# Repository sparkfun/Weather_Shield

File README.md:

SparkFun Weather Shield
========================

[*SparkFun Weather Shield (DEV-13956)*](https://www.sparkfun.com/products/13956)

Weather Shield is an Arduino shield that gathers relative humidity, barometric pressure, temperature, light intensity, as well as optional rain, wind direction, and wind speed (using optional [external weather gauges](https://www.sparkfun.com/products/8942)).

Repository Contents
------------------

* **/Firmware** - Example Arduino sketch to demostrate how to read from the various sensors.
* **/Fritzing** - Fritzing Example wiring images
* **/Hardware** - All the Eagle PCB design files (.brd, .sch).
* **/Production** - Test bed files and production panel files

Documentation
--------------
* **[Installing an Arduino Library Guide](https://learn.sparkfun.com/tutorials/installing-an-arduino-library)** - Basic information on how to install an Arduino library.
* **[MPL3115A2 Library](https://github.com/sparkfun/SparkFun_MPL3115A2_Breakout_Arduino_Library)** - MPL3115A2 library required for Weather Shield examples. 
* **[Si7021 Library](https://github.com/sparkfun/SparkFun_Si701_Breakout_Arduino_Library)** - Si7021 humidity sensor library required for Weather Shield examples. 
* **[Hookup Guide](https://learn.sparkfun.com/tutorials/arduino-weather-shield-hookup-guide-v12)** - Basic hookup guide for the Weather Shield v1.2.
* **[SparkFun Fritzing repo](https://github.com/sparkfun/Fritzing_Parts)** - Fritzing diagrams for SparkFun products.
* **[SparkFun 3D Model repo](https://github.com/sparkfun/3D_Models)** - 3D models of SparkFun products. 
* _**[HTU21D Library](https://github.com/sparkfun/SparkFun_HTU21D_Breakout_Arduino_Library)** - The HTU21D humidity sensor was used on DEV-12081 and prior versions of the Weather Shield so if you have an older version you may need this library to run the examples._

Product Versions
----------------
* [DEV-13956](https://www.sparkfun.com/products/13956)- V1.2 w/ Si7021
* _[DEV-12081 (Retired)](https://www.sparkfun.com/products/13956)- HTU21D_

Version History
---------------
* [v1.2](https://github.com/sparkfun/Weather_Shield/releases/tag/v1.2) - Latest Version
* [v1.1](https://github.com/sparkfun/Weather_Shield/releases/tag/v1.1) - Initial Release

License Information
-------------------

This product is _**open source**_! 

Please review the LICENSE.md file for license information. 

If you have any questions or concerns on licensing, please contact techsupport@sparkfun.com.

Distributed as-is; no warranty is given.

- Your friends at SparkFun.

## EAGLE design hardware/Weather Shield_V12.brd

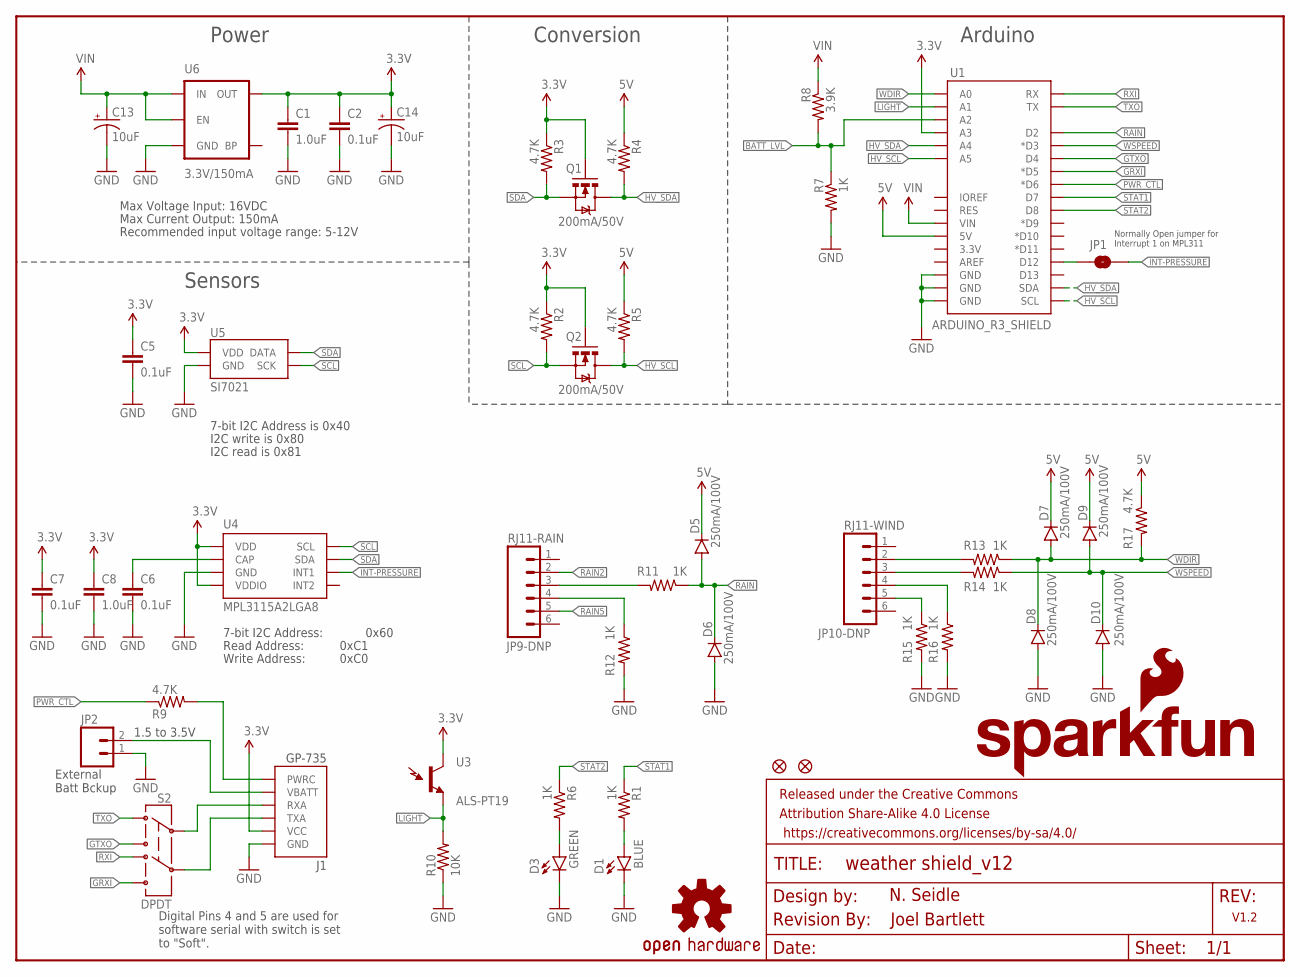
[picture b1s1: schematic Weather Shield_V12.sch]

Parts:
C1, C8: 1.0uF; 0603-CAP
C2, C5, C6, C7: 0.1uF; 0603-CAP
C13, C14: 10uF; EIA3216
D1: BLUE; LED-0603
D3: GREEN; LED-0603
D5, D6, D7, D8, D9, D10: 250mA/100V; SOD-323
FD1, FD2: FIDUCIAL1X2; FIDUCIAL-1X2
FRAME1: FRAME-LETTER; CREATIVE_COMMONS
J1: GP-735; GP-635T
JP1: JUMPER-PAD-2-NO; PAD-JUMPER-2-NO_NO_SILK
JP2: External Batt Bckup; 1X02
JP9-DNP: RJ11-RAIN; RJ11-6
JP10-DNP: RJ11-WIND; RJ11-6
LOGO1: OSHW-LOGOM; OSHW-LOGO-M
LOGO2: SFE_LOGO_NAME_FLAME.1_INCH; SFE_LOGO_NAME_FLAME_.1
Q1, Q2: 200mA/50V; SOT23-3
R1, R6, R7, R11, R12, R13, R14, R15, R16: 1K; 0603-RES
R2, R3, R4, R5, R9, R17: 4.7K; 0603-RES
R8: 3.9K; 0603
R10: 10K; 0603-RES
S2: DPDT; AYZ0202
U1: ARDUINO_R3_SHIELD; UNO_R3_SHIELD
U3: ALS-PT19
U4: MPL3115A2LGA8; LGA8
U5: SI7021
U6: 3.3V/150mA; SOT23-5
U$2: REVISION

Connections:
3.3V: C1.1, C2.1, C5.1, C7.1, C8.1, C14.A (+), J1.2 (VCC), Q1.1 (G), Q2.1 (G), R2.1, R3.1, U1.A3, U3.C (C1), U4.1 (VDD), U4.4 (VDDIO), U5.VDD, U6.5 (OUT)
3V_PWR_CTL: J1.6 (PWRC), R9.2
5V: D5.C, D7.C, D9.C, R4.1, R5.1, R17.1, U1.5V
BATT_LVL: R7.1, R8.2, U1.A2
GND: C1.2, C2.2, C5.2, C6.2, C7.2, C8.2, C13.C (-), C14.C (-), D1.C, D3.C, D6.A, D8.A, D10.A, J1.1 (GND), JP2.1, R7.2, R10.1, R12.2, R15.2, R16.2, U1.GND@0 (GND), U1.GND@1 (GND), U1.GND@2 (GND), U4.3 (GND), U5.GND, U6.2 (GND)
GPS-RX: J1.4 (RXA), S2.2
GPS-TX: J1.3 (TXA), S2.5
GRXI: S2.6, U1.D5 (*D5)
GTXO: S2.3, U1.D4
HV_SCL: Q2.3 (D), R5.2, U1.A5, U1.SCL
HV_SDA: Q1.3 (D), R4.2, U1.A4, U1.SDA
INT-PRESSURE: JP1.2, U4.6 (INT1)
LIGHT: R10.2, U1.A1, U3.E (E1)
unnamed: JP10-DNP.3, R14.2
unnamed: JP10-DNP.2, R13.2
unnamed: D1.A, R1.2
unnamed: JP9-DNP.3, R11.2
unnamed: C6.1, U4.2 (CAP)
unnamed: JP1.1, U1.D12
unnamed: D3.A, R6.2
unnamed: JP9-DNP.4, R12.1
unnamed: JP10-DNP.5, R15.1
unnamed: JP10-DNP.4, R16.1
PWR_CTL: R9.1, U1.D6 (*D6)
RAIN: D5.A, D6.C, R11.1, U1.D2
RAIN2: JP9-DNP.2
RAIN5: JP9-DNP.5
RXI: S2.4, U1.RX
SCL: Q2.2 (S), R2.2, U4.8 (SCL), U5.SCK
SDA: Q1.2 (S), R3.2, U4.7 (SDA), U5.DATA
STAT1: R1.1, U1.D7
STAT2: R6.1, U1.D8
TXO: S2.1, U1.TX
VIN: C13.A (+), R8.1, U1.VIN, U6.1 (IN), U6.3 (EN)
V_BATT: J1.5 (VBATT), JP2.2
WDIR: D7.A, D8.C, R13.1, R17.2, U1.A0
WSPEED: D9.A, D10.C, R14.1, U1.D3 (*D3)

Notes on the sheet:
Max Voltage Input: 16VDC
Max Current Output: 150mA
N. Seidle
Read Address:
Write Address:
7-bit I2C Address:
0x60
0xC1
0xC0
7-bit I2C Address is 0x40
I2C write is 0x80
I2C read is 0x81
1.5 to 3.5V
External Batt Bckup
Sensors
Power
Conversion
Arduino
V1.2
Digital Pins 4 and 5 are used for software serial with switch is set to "Soft".
Joel Bartlett
Recommended input voltage range: 5-12V
Normally Open jumper for Interrupt 1 on MPL311

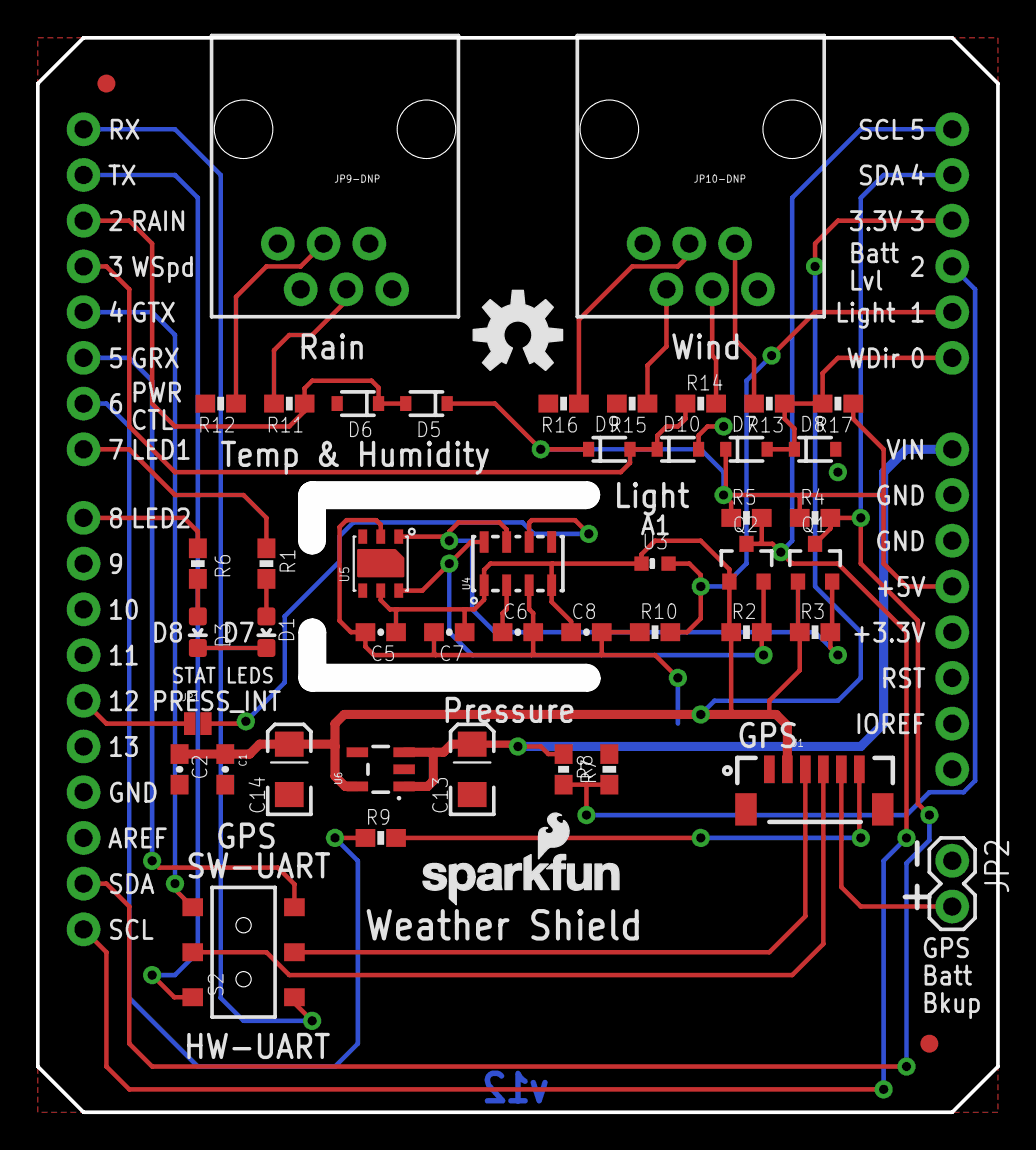
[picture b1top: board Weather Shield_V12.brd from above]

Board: 2 copper layers, 52.0 x 58.4 mm, 52 parts (0 on the bottom side), 35 nets.

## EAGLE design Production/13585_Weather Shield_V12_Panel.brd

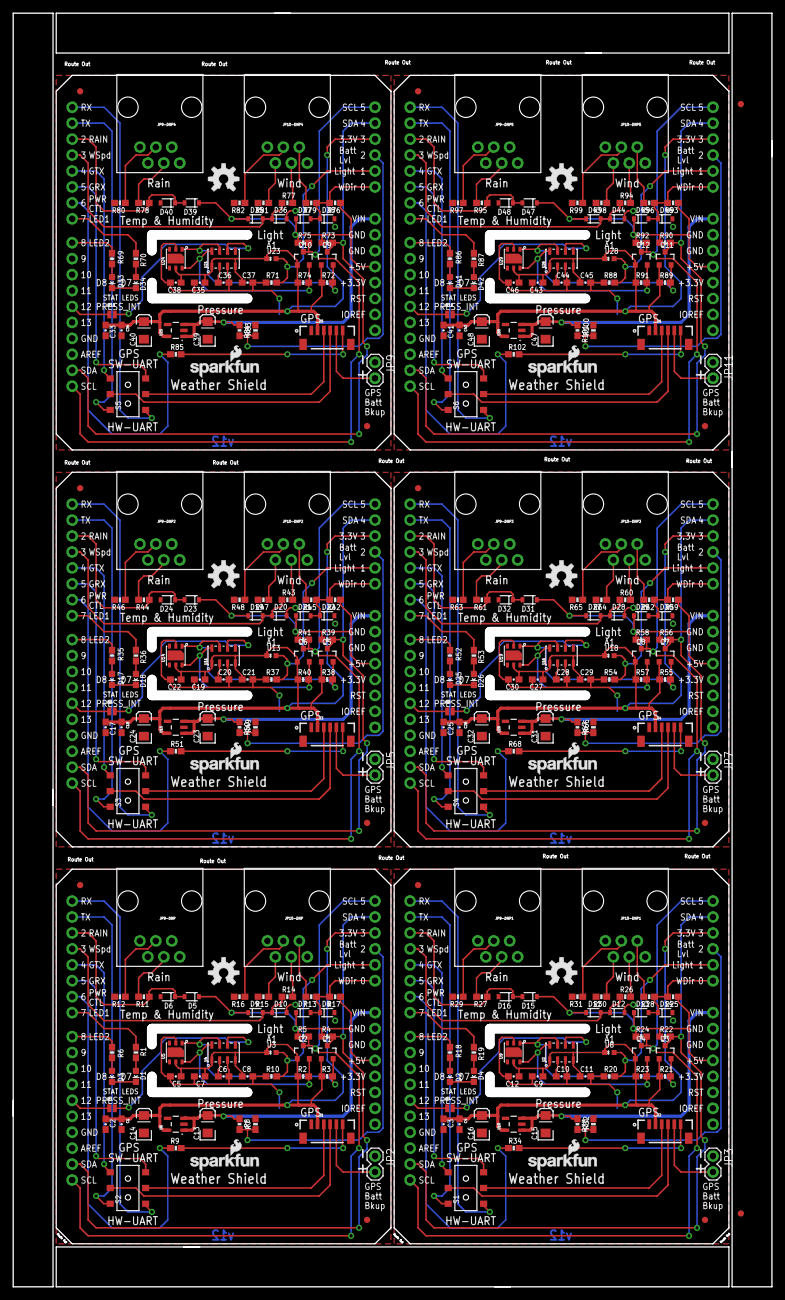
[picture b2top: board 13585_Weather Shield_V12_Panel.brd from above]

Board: 2 copper layers, 119.6 x 201.6 mm, 302 parts (0 on the bottom side), 210 nets.

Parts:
C1, C4, C8, C11, C18, C21, C26, C29, C34, C37, C42, C45: 1.0uF; 0603-CAP
C2, C3, C5, C6, C7, C9, C10, C12, C17, C19, C20, C22, C25, C27, C28, C30, C33, C35, C36, C38, C41, C43, C44, C46: 0.1uF; 0603-CAP
C13, C14, C15, C16, C23, C24, C31, C32, C39, C40, C47, C48: 10uF; EIA3216
D1, D4, D18, D26, D34, D42: BLUE; LED-0603
D2, D3, D17, D25, D33, D41: GREEN; LED-0603
D5, D6, D7, D8, D9, D10, D11, D12, D13, D14, D15, D16, D19, D20, D21, D22, D23, D24, D27, D28, D29, D30, D31, D32, D35, D36, D37, D38, D39, D40, D43, D44, D45, D46, D47, D48: 250mA/100V; SOD-323
E$7, E$8: FIDUCIAL-1X2
FD1, FD2, FD3, FD4, FD5, FD6, FD7, FD8, FD9, FD10, FD11, FD12: FIDUCIAL1X2; FIDUCIAL-1X2
J1, J2, J3, J4, J5, J6: GP-735; GP-635T
JP1, JP4, JP6, JP8, JP10, JP12: PAD-JUMPER-2-NO_NO_SILK
JP2, JP3, JP5, JP7, JP9, JP11: External Batt Bckup; 1X02
JP9-DNP, JP9-DNP1, JP9-DNP2, JP9-DNP3, JP9-DNP4, JP9-DNP5: RJ11-RAIN; RJ11-6
JP10-DNP, JP10-DNP1, JP10-DNP2, JP10-DNP3, JP10-DNP4, JP10-DNP5: RJ11-WIND; RJ11-6
LOGO1, LOGO4, LOGO6, LOGO8, LOGO10, LOGO12: OSHW-LOGOM; OSHW-LOGO-M
LOGO2, LOGO3, LOGO5, LOGO7, LOGO9, LOGO11: SFE_LOGO_NAME_FLAME.1_INCH; SFE_LOGO_NAME_FLAME_.1
Q1, Q2, Q3, Q4, Q5, Q6, Q7, Q8, Q9, Q10, Q11, Q12: 200mA/50V; SOT23-3
R1, R6, R7, R11, R12, R13, R14, R15, R16, R18, R19, R26, R27, R28, R29, R30, R31, R32, R35, R36, R43, R44, R45, R46, R47, R48, R49, R52, R53, R60, R61, R62, R63, R64, R65, R66, R69, R70, R77, R78, R79, R80, R81, R82, R83, R86, R87, R94, R95, R96, R97, R98, R99, R100: 1K; 0603-RES
R2, R3, R4, R5, R9, R17, R21, R22, R23, R24, R25, R34, R38, R39, R40, R41, R42, R51, R55, R56, R57, R58, R59, R68, R72, R73, R74, R75, R76, R85, R89, R90, R91, R92, R93, R102: 4.7K; 0603-RES
R8, R33, R50, R67, R84, R101: 3.9K; 0603
R10, R20, R37, R54, R71, R88: 10K; 0603-RES
S1, S2, S3, S4, S5, S6: DPDT; AYZ0202
U1, U7, U12, U17, U22, U27: ARDUINO_R3_SHIELD; UNO_R3_SHIELD
U2, U4, U11, U16, U21, U26: MPL3115A2LGA8; LGA8
U3, U8, U13, U18, U23, U28: ALS-PT19
U5, U9, U14, U19, U24, U29: SI7021
U6, U10, U15, U20, U25, U30: 3.3V/150mA; SOT23-5

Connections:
3.3V: C1.1, C2.1, C5.1, C7.1, C8.1, C14.A, J1.2, Q1.1, Q2.1, R2.1, R3.1, U1.A3, U3.C, U4.1, U4.4, U5.VDD, U6.5
3.3V1: C3.1, C4.1, C9.1, C11.1, C12.1, C16.A, J2.2, Q3.1, Q4.1, R21.1, R23.1, U2.1, U2.4, U7.A3, U8.C, U9.VDD, U10.5
3.3V2: C17.1, C18.1, C19.1, C21.1, C22.1, C24.A, J3.2, Q5.1, Q6.1, R38.1, R40.1, U11.1, U11.4, U12.A3, U13.C, U14.VDD, U15.5
3.3V3: C25.1, C26.1, C27.1, C29.1, C30.1, C32.A, J4.2, Q7.1, Q8.1, R55.1, R57.1, U16.1, U16.4, U17.A3, U18.C, U19.VDD, U20.5
3.3V4: C33.1, C34.1, C35.1, C37.1, C38.1, C40.A, J5.2, Q9.1, Q10.1, R72.1, R74.1, U21.1, U21.4, U22.A3, U23.C, U24.VDD, U25.5
3.3V5: C41.1, C42.1, C43.1, C45.1, C46.1, C48.A, J6.2, Q11.1, Q12.1, R89.1, R91.1, U26.1, U26.4, U27.A3, U28.C, U29.VDD, U30.5
3V_PWR_CTL: J1.6, R9.2
3V_PWR_CTL1: J2.6, R34.2
3V_PWR_CTL2: J3.6, R51.2
3V_PWR_CTL3: J4.6, R68.2
3V_PWR_CTL4: J5.6, R85.2
3V_PWR_CTL5: J6.6, R102.2
5V: D5.C, D7.C, D9.C, R4.1, R5.1, R17.1, U1.5V
5V1: D11.C, D13.C, D15.C, R22.1, R24.1, R25.1, U7.5V
5V2: D19.C, D21.C, D23.C, R39.1, R41.1, R42.1, U12.5V
5V3: D27.C, D29.C, D31.C, R56.1, R58.1, R59.1, U17.5V
5V4: D35.C, D37.C, D39.C, R73.1, R75.1, R76.1, U22.5V
5V5: D43.C, D45.C, D47.C, R90.1, R92.1, R93.1, U27.5V
BATT_LVL: R7.1, R8.2, U1.A2
BATT_LVL1: R32.1, R33.2, U7.A2
BATT_LVL2: R49.1, R50.2, U12.A2
BATT_LVL3: R66.1, R67.2, U17.A2
BATT_LVL4: R83.1, R84.2, U22.A2
BATT_LVL5: R100.1, R101.2, U27.A2
GND: C1.2, C2.2, C5.2, C6.2, C7.2, C8.2, C13.C, C14.C, D1.C, D3.C, D6.A, D8.A, D10.A, J1.1, JP2.1, R7.2, R10.1, R12.2, R15.2, R16.2, U1.GND@0, U1.GND@1, U1.GND@2, U4.3, U5.GND, U6.2
GND1: C3.2, C4.2, C9.2, C10.2, C11.2, C12.2, C15.C, C16.C, D2.C, D4.C, D12.A, D14.A, D16.A, J2.1, JP3.1, R20.1, R29.2, R30.2, R31.2, R32.2, U2.3, U7.GND@0, U7.GND@1, U7.GND@2, U9.GND, U10.2
GND2: C17.2, C18.2, C19.2, C20.2, C21.2, C22.2, C23.C, C24.C, D17.C, D18.C, D20.A, D22.A, D24.A, J3.1, JP5.1, R37.1, R46.2, R47.2, R48.2, R49.2, U11.3, U12.GND@0, U12.GND@1, U12.GND@2, U14.GND, U15.2
GND3: C25.2, C26.2, C27.2, C28.2, C29.2, C30.2, C31.C, C32.C, D25.C, D26.C, D28.A, D30.A, D32.A, J4.1, JP7.1, R54.1, R63.2, R64.2, R65.2, R66.2, U16.3, U17.GND@0, U17.GND@1, U17.GND@2, U19.GND, U20.2
GND4: C33.2, C34.2, C35.2, C36.2, C37.2, C38.2, C39.C, C40.C, D33.C, D34.C, D36.A, D38.A, D40.A, J5.1, JP9.1, R71.1, R80.2, R81.2, R82.2, R83.2, U21.3, U22.GND@0, U22.GND@1, U22.GND@2, U24.GND, U25.2
GND5: C41.2, C42.2, C43.2, C44.2, C45.2, C46.2, C47.C, C48.C, D41.C, D42.C, D44.A, D46.A, D48.A, J6.1, JP11.1, R88.1, R97.2, R98.2, R99.2, R100.2, U26.3, U27.GND@0, U27.GND@1, U27.GND@2, U29.GND, U30.2
GPS-RX: J1.4, S2.2
GPS-RX1: J2.4, S1.2
GPS-RX2: J3.4, S3.2
GPS-RX3: J4.4, S4.2
GPS-RX4: J5.4, S5.2
GPS-RX5: J6.4, S6.2
GPS-TX: J1.3, S2.5
GPS-TX1: J2.3, S1.5
GPS-TX2: J3.3, S3.5
GPS-TX3: J4.3, S4.5
GPS-TX4: J5.3, S5.5
GPS-TX5: J6.3, S6.5
GRXI: S2.6, U1.D5
GRXI1: S1.6, U7.D5
GRXI2: S3.6, U12.D5
GRXI3: S4.6, U17.D5
GRXI4: S5.6, U22.D5
GRXI5: S6.6, U27.D5
GTXO: S2.3, U1.D4
GTXO1: S1.3, U7.D4
GTXO2: S3.3, U12.D4
GTXO3: S4.3, U17.D4
GTXO4: S5.3, U22.D4
GTXO5: S6.3, U27.D4
HV_SCL: Q2.3, R5.2, U1.A5, U1.SCL
HV_SCL1: Q4.3, R24.2, U7.A5, U7.SCL
HV_SCL2: Q6.3, R41.2, U12.A5, U12.SCL
HV_SCL3: Q8.3, R58.2, U17.A5, U17.SCL
HV_SCL4: Q10.3, R75.2, U22.A5, U22.SCL
HV_SCL5: Q12.3, R92.2, U27.A5, U27.SCL
HV_SDA: Q1.3, R4.2, U1.A4, U1.SDA
HV_SDA1: Q3.3, R22.2, U7.A4, U7.SDA
HV_SDA2: Q5.3, R39.2, U12.A4, U12.SDA
HV_SDA3: Q7.3, R56.2, U17.A4, U17.SDA
HV_SDA4: Q9.3, R73.2, U22.A4, U22.SDA
HV_SDA5: Q11.3, R90.2, U27.A4, U27.SDA
INT-PRESSURE: JP1.2, U4.6
INT-PRESSURE1: JP4.2, U2.6
INT-PRESSURE2: JP6.2, U11.6
INT-PRESSURE3: JP8.2, U16.6
INT-PRESSURE4: JP10.2, U21.6
INT-PRESSURE5: JP12.2, U26.6
LIGHT: R10.2, U1.A1, U3.E
LIGHT1: R20.2, U7.A1, U8.E
LIGHT2: R37.2, U12.A1, U13.E
LIGHT3: R54.2, U17.A1, U18.E
LIGHT4: R71.2, U22.A1, U23.E
LIGHT5: R88.2, U27.A1, U28.E
unnamed: JP10-DNP.3, R14.2
unnamed: JP10-DNP.2, R13.2
unnamed: D1.A, R1.2
unnamed: JP9-DNP.3, R11.2
unnamed: C6.1, U4.2
unnamed: JP1.1, U1.D12
unnamed: D3.A, R6.2
unnamed: D2.A, R18.2
unnamed: D4.A, R19.2
unnamed: C10.1, U2.2
unnamed: JP9-DNP.4, R12.1
unnamed: JP10-DNP.5, R15.1
unnamed: JP10-DNP.4, R16.1
unnamed: JP10-DNP1.2, R28.2
unnamed: JP10-DNP1.3, R26.2
unnamed: JP9-DNP1.3, R27.2
unnamed: JP9-DNP1.4, R29.1
unnamed: JP10-DNP1.5, R30.1
unnamed: JP10-DNP1.4, R31.1
unnamed: JP4.1, U7.D12
unnamed: D17.A, R35.2
unnamed: D18.A, R36.2
unnamed: C20.1, U11.2
unnamed: JP10-DNP2.2, R45.2
unnamed: JP10-DNP2.3, R43.2
unnamed: JP9-DNP2.3, R44.2
unnamed: JP9-DNP2.4, R46.1
unnamed: JP10-DNP2.5, R47.1
unnamed: JP10-DNP2.4, R48.1
unnamed: JP6.1, U12.D12
unnamed: D25.A, R52.2
unnamed: D26.A, R53.2
unnamed: C28.1, U16.2
unnamed: JP10-DNP3.2, R62.2
unnamed: JP10-DNP3.3, R60.2
unnamed: JP9-DNP3.3, R61.2
unnamed: JP9-DNP3.4, R63.1
unnamed: JP10-DNP3.5, R64.1
unnamed: JP10-DNP3.4, R65.1
unnamed: JP8.1, U17.D12
unnamed: D33.A, R69.2
unnamed: D34.A, R70.2
unnamed: C36.1, U21.2
unnamed: JP10-DNP4.2, R79.2
unnamed: JP10-DNP4.3, R77.2
unnamed: JP9-DNP4.3, R78.2
unnamed: JP9-DNP4.4, R80.1
unnamed: JP10-DNP4.5, R81.1
unnamed: JP10-DNP4.4, R82.1
unnamed: JP10.1, U22.D12
unnamed: D41.A, R86.2
unnamed: D42.A, R87.2
unnamed: C44.1, U26.2
unnamed: JP10-DNP5.2, R96.2
unnamed: JP10-DNP5.3, R94.2
unnamed: JP9-DNP5.3, R95.2
unnamed: JP9-DNP5.4, R97.1
unnamed: JP10-DNP5.5, R98.1
unnamed: JP10-DNP5.4, R99.1
unnamed: JP12.1, U27.D12
PWR_CTL: R9.1, U1.D6
PWR_CTL1: R34.1, U7.D6
PWR_CTL2: R51.1, U12.D6
PWR_CTL3: R68.1, U17.D6
PWR_CTL4: R85.1, U22.D6
PWR_CTL5: R102.1, U27.D6
RAIN: D5.A, D6.C, R11.1, U1.D2
RAIN1: D15.A, D16.C, R27.1, U7.D2
RAIN6: D23.A, D24.C, R44.1, U12.D2
RAIN9: D31.A, D32.C, R61.1, U17.D2
RAIN12: D39.A, D40.C, R78.1, U22.D2
RAIN15: D47.A, D48.C, R95.1, U27.D2
RXI: S2.4, U1.RX
RXI1: S1.4, U7.RX
RXI2: S3.4, U12.RX
RXI3: S4.4, U17.RX
RXI4: S5.4, U22.RX
RXI5: S6.4, U27.RX
SCL: Q2.2, R2.2, U4.8, U5.SCK
SCL1: Q4.2, R23.2, U2.8, U9.SCK
SCL2: Q6.2, R40.2, U11.8, U14.SCK
SCL3: Q8.2, R57.2, U16.8, U19.SCK
SCL4: Q10.2, R74.2, U21.8, U24.SCK
SCL5: Q12.2, R91.2, U26.8, U29.SCK
SDA: Q1.2, R3.2, U4.7, U5.DATA
SDA1: Q3.2, R21.2, U2.7, U9.DATA
SDA2: Q5.2, R38.2, U11.7, U14.DATA
SDA3: Q7.2, R55.2, U16.7, U19.DATA
SDA4: Q9.2, R72.2, U21.7, U24.DATA
SDA5: Q11.2, R89.2, U26.7, U29.DATA
STAT1: R1.1, U1.D7
STAT2: R6.1, U1.D8
STAT3: R18.1, U7.D8
STAT4: R19.1, U7.D7
STAT5: R35.1, U12.D8
STAT6: R36.1, U12.D7
STAT7: R52.1, U17.D8
STAT8: R53.1, U17.D7
STAT9: R69.1, U22.D8
STAT10: R70.1, U22.D7
STAT11: R86.1, U27.D8
STAT12: R87.1, U27.D7
TXO: S2.1, U1.TX
TXO1: S1.1, U7.TX
TXO2: S3.1, U12.TX
TXO3: S4.1, U17.TX
TXO4: S5.1, U22.TX
TXO5: S6.1, U27.TX
VIN: C13.A, R8.1, U1.VIN, U6.1, U6.3
VIN1: C15.A, R33.1, U7.VIN, U10.1, U10.3
VIN2: C23.A, R50.1, U12.VIN, U15.1, U15.3
VIN3: C31.A, R67.1, U17.VIN, U20.1, U20.3
VIN4: C39.A, R84.1, U22.VIN, U25.1, U25.3
VIN5: C47.A, R101.1, U27.VIN, U30.1, U30.3
V_BATT: J1.5, JP2.2
V_BATT1: J2.5, JP3.2
V_BATT2: J3.5, JP5.2
V_BATT3: J4.5, JP7.2
V_BATT4: J5.5, JP9.2
V_BATT5: J6.5, JP11.2
WDIR: D7.A, D8.C, R13.1, R17.2, U1.A0
WDIR1: D13.A, D14.C, R25.2, R28.1, U7.A0
WDIR2: D21.A, D22.C, R42.2, R45.1, U12.A0
WDIR3: D29.A, D30.C, R59.2, R62.1, U17.A0
WDIR4: D37.A, D38.C, R76.2, R79.1, U22.A0
WDIR5: D45.A, D46.C, R93.2, R96.1, U27.A0
WSPEED: D9.A, D10.C, R14.1, U1.D3
WSPEED1: D11.A, D12.C, R26.1, U7.D3
WSPEED2: D19.A, D20.C, R43.1, U12.D3
WSPEED3: D27.A, D28.C, R60.1, U17.D3
WSPEED4: D35.A, D36.C, R77.1, U22.D3
WSPEED5: D43.A, D44.C, R94.1, U27.D3

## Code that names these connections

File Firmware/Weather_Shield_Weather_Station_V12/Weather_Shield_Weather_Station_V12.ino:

/*
  Weather Shield Example
  By: Nathan Seidle
  SparkFun Electronics
  Date: November 16th, 2013
  License: This code is public domain but you buy me a beer if you use this and we meet someday (Beerware license).

  Much of this is based on Mike Grusin's USB Weather Board code: https://www.sparkfun.com/products/10586

  This is a more advanced example of how to utilize every aspect of the weather shield. See the basic
  example if you're just getting started.

  This code reads all the various sensors (wind speed, direction, rain gauge, humidity, pressure, light, batt_lvl)
  and reports it over the serial comm port. This can be easily routed to a datalogger (such as OpenLog) or
  a wireless transmitter (such as Electric Imp).

  Measurements are reported once a second but windspeed and rain gauge are tied to interrupts that are
  calculated at each report.

  This example code assumes the GPS module is not used.

  Updated by Joel Bartlett
  03/02/2017
  Removed HTU21D code and replaced with Si7021

  Updated be Wes Furuya
  06/19/2023
  Implemented "Weather Meter" Arduino library
*/

#include <Wire.h>                                        //I2C needed for sensors
#include "SparkFunMPL3115A2.h"                           //Pressure sensor - Search "SparkFun MPL3115" and install from Library Manager
#include "SparkFun_Si7021_Breakout_Library.h"            //Humidity sensor - Search "SparkFun Si7021" and install from Library Manager
#include "SparkFun_Weather_Meter_Kit_Arduino_Library.h"  //Weather meter kit - Search "SparkFun Weather Meter" and install from Library Manager


//Hardware pin definitions
//-=-=-=-=-=-=-=-=-=-=-=-=-=-=-=-=-=-=-=-=-=-=-=-=-=-=-=-=
// digital I/O pins
const byte WSPEED = 3;
const byte RAIN = 2;
const byte STAT1 = 7;
const byte STAT2 = 8;

// analog I/O pins
const byte REFERENCE_3V3 = A3;
const byte LIGHT = A1;
const byte BATT = A2;
const byte WDIR = A0;
//-=-=-=-=-=-=-=-=-=-=-=-=-=-=-=-=-=-=-=-=-=-=-=-=-=-=-=-=

//Global Variables
//-=-=-=-=-=-=-=-=-=-=-=-=-=-=-=-=-=-=-=-=-=-=-=-=-=-=-=-=
long lastSecond;  //The millis counter to see when a second rolls by

float humidity = 0;  // [%]
float tempf = 0;     // [temperature F]
//float baromin = 30.03;// [barom in] - It's hard to calculate baromin locally, do this in the agent
float pressure = 0;

float wind_dir = 0;    // [degrees (Cardinal)]
float wind_speed = 0;  // [kph]
float rain = 0;        // [mm]

float batt_lvl = 11.8;  //[analog value from 0 to 1023]
float light_lvl = 455;  //[analog value from 0 to 1023]
//-=-=-=-=-=-=-=-=-=-=-=-=-=-=-=-=-=-=-=-=-=-=-=-=-=-=-=-=


MPL3115A2 myPressure;                                      //Create an instance of the pressure sensor
Weather myHumidity;                                        //Create an instance of the humidity sensor
SFEWeatherMeterKit myweatherMeterKit(WDIR, WSPEED, RAIN);  // Create an instance of the weather meter kit


void setup() {
  Serial.begin(115200);
  Serial.println("Weather Shield Example");

  pinMode(STAT1, OUTPUT);  //Status LED Blue
  pinMode(STAT2, OUTPUT);  //Status LED Green

  // pinMode(WSPEED, INPUT_PULLUP); // input from wind meters windspeed sensor
  // pinMode(RAIN, INPUT_PULLUP); // input from wind meters rain gauge sensor

  pinMode(REFERENCE_3V3, INPUT);
  pinMode(LIGHT, INPUT);

  //Configure the pressure sensor
  myPressure.begin();               // Get sensor online
  myPressure.setModeBarometer();    // Measure pressure in Pascals from 20 to 110 kPa
  myPressure.setOversampleRate(7);  // Set Oversample to the recommended 128
  myPressure.enableEventFlags();    // Enable all three pressure and temp event flags

  //Configure the humidity sensor
  myHumidity.begin();

  // The weather meter kit library assumes a 12-bit ADC
  // Configuring a 10-bit ADC resolution for the ATmega328 (RedBoard/Uno)
  myweatherMeterKit.setADCResolutionBits(10);

  // Begin weather meter kit
  myweatherMeterKit.begin();

  lastSecond = millis();

  // // attach external interrupt pins to IRQ functions
  // attachInterrupt(0, rainIRQ, FALLING);
  // attachInterrupt(1, wspeedIRQ, FALLING);

  // // turn on interrupts
  // interrupts();

  Serial.println("Weather Shield online!");
}

void loop() {
  //Keep track of which minute it is
  if (millis() - lastSecond >= 1000) {
    digitalWrite(STAT1, HIGH);  //Blink stat LED

    lastSecond += 1000;

    //Report all readings every second
    printWeather();
  }

  digitalWrite(STAT1, LOW);  //Turn off stat LED

  delay(100);
}

//Calculates each of the variables that wunderground is expecting
void calcWeather() {

  //Calc temp/humidity from Si7021 sensor
  humidity = myHumidity.getRH();
  tempf = myHumidity.readTempF();

  //Weather Meter Kit
  //Calc Wind
  wind_dir = myweatherMeterKit.getWindDirection();
  wind_speed = myweatherMeterKit.getWindSpeed();
  //Calc Rain
  rain = myweatherMeterKit.getTotalRainfall();

  //Calc pressure from MPL3115A2
  pressure = myPressure.readPressure();

  //Calc light level
  light_lvl = get_light_level();

  //Calc battery level
  batt_lvl = get_battery_level();
}

//Returns the voltage of the light sensor based on the 3.3V rail
//This allows us to ignore what VCC might be (an Arduino plugged into USB has VCC of 4.5 to 5.2V)
float get_light_level() {
  float operatingVoltage = analogRead(REFERENCE_3V3);

  float lightSensor = analogRead(LIGHT);

  operatingVoltage = 3.3 / operatingVoltage;  //The reference voltage is 3.3V

  lightSensor = operatingVoltage * lightSensor;

  return (lightSensor);
}

//Returns the voltage of the raw pin based on the 3.3V rail
//This allows us to ignore what VCC might be (an Arduino plugged into USB has VCC of 4.5 to 5.2V)
//Battery level is connected to the RAW pin on Arduino and is fed through two 5% resistors:
//3.9K on the high side (R1), and 1K on the low side (R2)
float get_battery_level() {
  float operatingVoltage = analogRead(REFERENCE_3V3);

  float rawVoltage = analogRead(BATT);

  operatingVoltage = 3.30 / operatingVoltage;  //The reference voltage is 3.3V

  rawVoltage = operatingVoltage * rawVoltage;  //Convert the 0 to 1023 int to actual voltage on BATT pin

  rawVoltage *= 4.90;  //(3.9k+1k)/1k - multiple BATT voltage by the voltage divider to get actual system voltage

  return (rawVoltage);
}


//Prints the various variables directly to the port
//I don't like the way this function is written but Arduino doesn't support floats under sprintf
void printWeather() {
  calcWeather();  //Go calc all the various sensors

  Serial.println();
  Serial.print("humidity=");
  Serial.print(humidity, 1);
  Serial.print(" %RH, tempf=");
  Serial.print(tempf, 1);
  Serial.print(" F, pressure=");
  Serial.print(pressure, 2);
  Serial.print(" Pa, wind direction= ");
  Serial.print(wind_dir, 1);
  Serial.print(" deg, wind speed= ");
  Serial.print(wind_speed, 1);
  Serial.print(" kph, total rain= ");
  Serial.print(rain, 1);
  Serial.print(" mm, batt_lvl=");
  Serial.print(batt_lvl, 2);
  Serial.print(" V, light_lvl=");
  Serial.print(light_lvl, 2);
  Serial.print(",");
  Serial.println("#");
}

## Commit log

2013-09-20 Initial commit of v10 hardware.
2013-09-20 Added analog sense on VIN/Batt level.
2013-09-20 Reduction of ground plane around sensors.
2013-09-20 Small silk changes.
2013-09-22 Added power ctl to GPS and backup battery connection.
2013-09-22 Tweaked schematic labels and connector for backup battery.
2013-09-22 Added support for smaller, cheaper ALS-PT19 light sensor.
2013-10-14 v1.1 that addresses many issues.
    Many schematic and routing changes. See issues.
2013-10-14 Added milling slots and updated readme.
    Added slots to allow better airflow around sensors.
2013-10-14 Panel Created
2013-11-16 Example firmware now works
2013-11-16 Update to readme.
2013-11-16 Adding GPS example
2013-11-16 Simplified GPS example sketch with new TinyGPS++ library.
2013-11-16 Small cleanup of schematic.
2013-12-04 Added fritzing part.
2013-12-05 Updating README
2014-08-27 Update README.md
    Adding explicit note for additional libraries location to run demo code.
2015-02-12 Bug call getWindSpeed twice get Nan result
2015-09-11 Fixed NaN bug. See bug 15.
2015-10-13 Fixing library include statements, updating README, fixing directory structure
2015-10-27 Leverage Git Submodules to pull in required libraries.
2016-01-21 Fritzing File Moved
    Fritzing file now located in Fritzng_Parts
2016-06-10 Adding more basic example. Renaming weather station example.
2016-06-10 Cleaning up examples and adding pointers to where to get libraries.
2016-06-10 Small bug fix to NaN error.
2016-08-12 Fixing output to serial monitor for longitude
    changed line 445 to Serial.print(",lng="); to fix this issue:
    https://github.com/sparkfun/Weather_Shield/issues/23
2016-08-12 Fixing output for windspeedmph
    Adding line of code at 178:
    windspeedmph = currentSpeed;//update global variable for windspeed when using the printWeather() function
    and added comment to line 227 to explain why the calculation was commented out:
    //windspeedmph = get_wind_speed(); //This is calculated in the main loop on line 179
    to fix this issue => https://github.com/sparkfun/Weather_Shield/issues/24
2016-08-12 Formatting
    formatting code on line 179
2016-08-18 V1.2 Initial Checklist pushes
2016-08-24 Fixed 4-way junctions
    Fixed 4-way junctions
2016-08-25 Post group review changes
2016-09-27 Post QC Checklist fixes
    Addressed the few issues that came up during the preliminary QC
    checklist. Mostly PROD_IDs missing and aesthetic fixes.
2016-10-24 Removed hard-coded error numbers. Updated ignore to avoid lock files.
2016-11-01 Updated Si7021 footprint
    Updated Si7021 footprint with correct center paste paste.
2016-11-08 Pushing fixes to Si7021 IC footprint tSTOP
2016-11-30 Slight modifications before final review
    Moved logos to avoid cover up by GPS. Moved GPS backup batter
    connection. Change jumper on D12 to NO instead of NC.
2016-11-30 Moved logo
2016-12-01 Minor Changes after group review for Reds
    Fixed text under VREG to have correct info, fixed Eagle error on J1
    (GPS Conn), fixed overlapping values, minor silk changes, moved via,
    updated HW/SW serial switch text to modern standard .
2016-12-09 Final issue fixes before going out for reds.
2016-12-15 panel
2017-03-02 Updated code for new revision V12
2017-03-02 Small fix to GPS example
2017-06-22 Fix issue w/ windspeedmph in Weather Shield w/ GPS
    I fixed the issue with the _windspeedmph_ in the _Weather_Shield_Weather_Station.ino_ example code [ [https://github.com/sparkfun/Weather_Shield/pull/25](https://github.com/sparkfun/Weather_Shield/pu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
2018-11-03 Update readme to point to newer Si7021 humidity sensor lib
2019-01-12 replaced the original with the example in the sparkfun site and fixed the wind speed bug.
2019-02-18 Delete Weather_Shield_Basic_V12.ino.ino
    Remove duplicate without Joel's Note
2019-02-18 Update Path for Basic Code
    -change folder name to be consistent with V12 code
2019-02-18 Update README.md
    -update image for latest board
    -update sku
2019-02-18 Update README.md
    -Update Tutorial Link to V12
2019-02-18 Fix Minor Issues
    -Fix output for windspeedmph related to this issue that was not updated in this version of code [ [https://github.com/sparkfun/Weather_Shield/commit/cb2b3dee3dc1f11ecff50dbc76434f29dbfc3372](https://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
    - Fixing output to serial monitor for longitude that was not updated in this version of code [ [https://github.com/sparkfun/Weather_Shield/commit/d09a0d830e3668e70adf77a1f900ca0f23c9663b](https://git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
2019-02-18 Minor Update Path Name
    -Change folder name to Capital letters for firmware and hardware
2019-02-18 Removing Duplicate Paths
2019-02-18 Re-add Folders
    Re-add examples and hardware folder
2019-02-18 Update Weather_Shield_Weather_Station_V12.ino
    - Auto Format
2019-02-18 Autoformat
    Code was not rending properly online, using the autoformat in Arduino for better viewing.
2022-06-23 * Changing Pressure reading to pressure_raw * Adding Pressure Normalization function to Sea Level equiv to output
2023-07-04 Update Code
    Modified code to utilize new "Weather Meter Kit" Arduino library
    Included small updates for the "TinyGPSPlus" Arduino library
    Reconfigured baud rate to 115200bps

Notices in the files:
parts and their libraries:
SparkFun-Sensors: Licensing: CC v3.0 Share-Alike You are welcome to use this library for commercial purposes.
SparkFun-Capacitors: Licensing: Creative Commons ShareAlike 4.0 International - https://creativecommons.org/licenses/by-sa/4.0
SparkFun-Aesthetics: Released under the Creative Commons
